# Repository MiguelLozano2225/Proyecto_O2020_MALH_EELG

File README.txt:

El fin de este repositorio es que se tenga un conjunto de todos los códigos que se hicieron para la finalización de este proyecto.

Incluye los códigos:
	-K64F
	-KW36 (Conectado a la laptop)
	-KW36 (Conetactado a la K64F)
	-Proyectos de Java

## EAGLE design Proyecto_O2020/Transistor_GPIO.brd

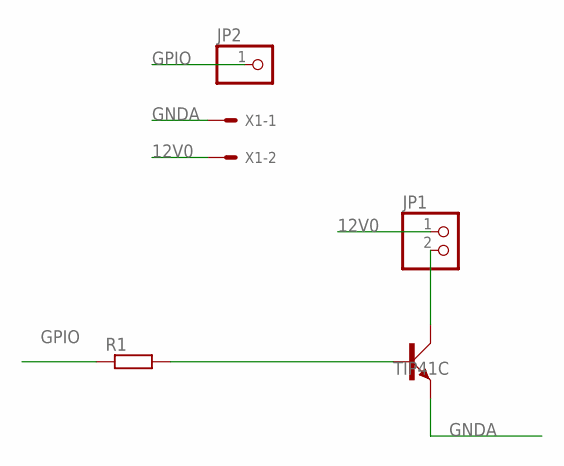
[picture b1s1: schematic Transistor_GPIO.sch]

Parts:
JP1: PINHD-1X2; 1X02
JP2: PINHD-1X1; 1X01
Q1: TIP41C; TO220AV
R1: R-EU_0207/10; 0207/10
X1: KK-156-2

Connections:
12V0: JP1.1, X1.2
GNDA: Q1.E, X1.1
GPIO: JP2.1, R1.1
unnamed: JP1.2, Q1.C
unnamed: Q1.B, R1.2

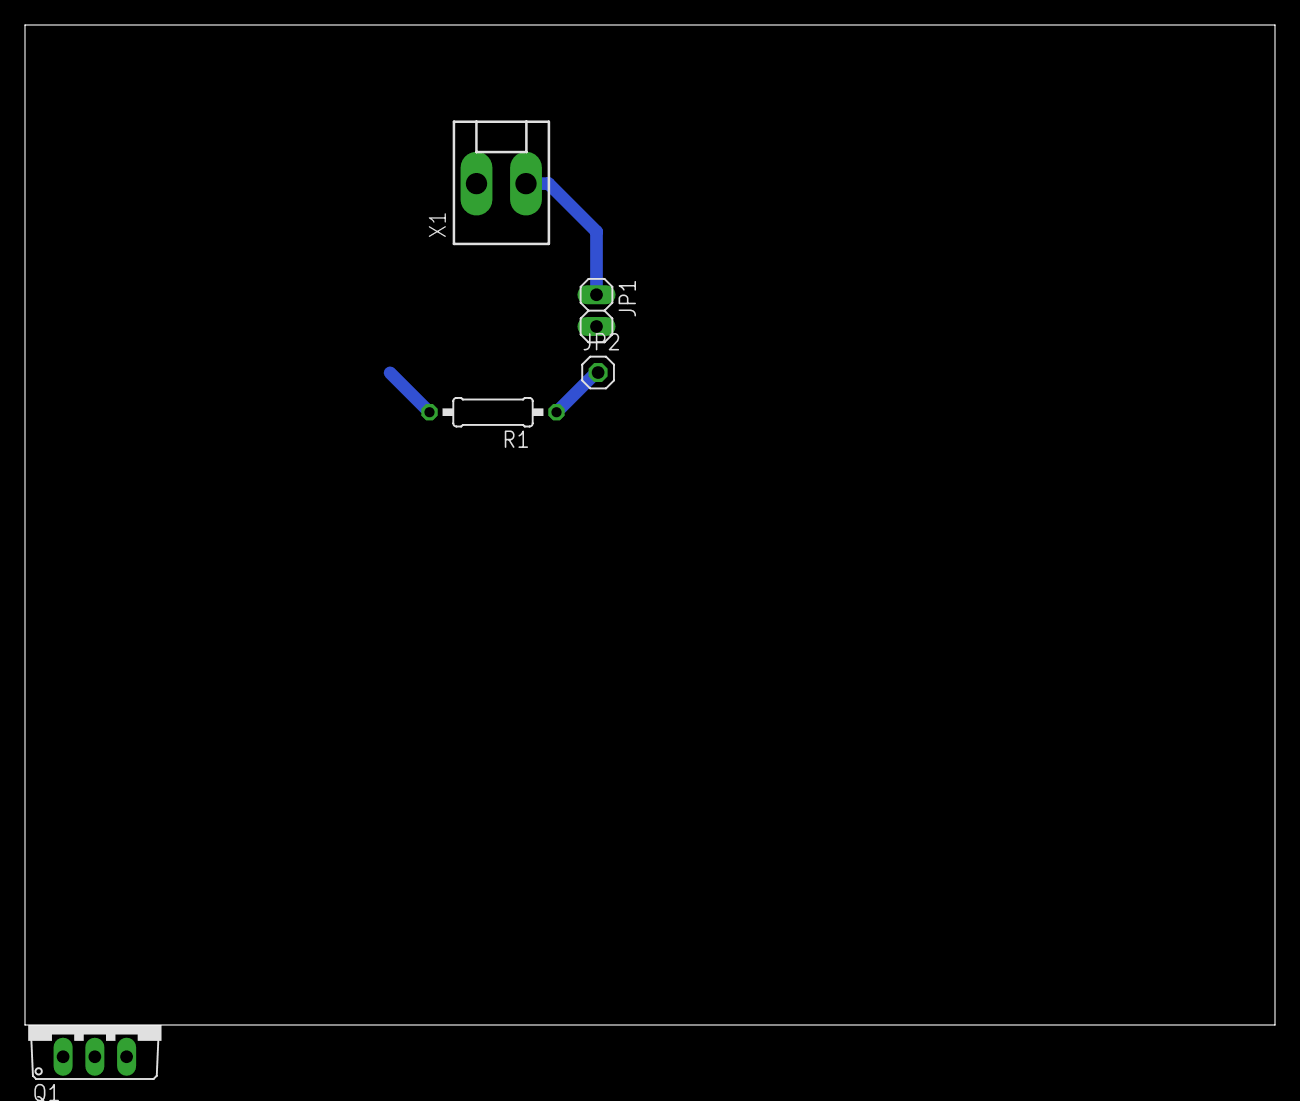
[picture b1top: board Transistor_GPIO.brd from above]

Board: 2 copper layers, 100.0 x 80.0 mm, 5 parts (0 on the bottom side), 5 nets.

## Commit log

2020-11-24 Los códigos de la tarjetas K64F y KW36 han sido añadidos, asi como los proyectos de Java para la interfaz de la computadora
2020-11-25 EAGLE files has been added
